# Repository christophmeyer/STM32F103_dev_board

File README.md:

# STM32F103 Development Board

This repo contains the [KiCad](https://www.kicad.org/) hardware design files for a development board for the `STM32F103` MCU, which is somewhat similar to the well known blue pill board. The design(er) has greatly benefitted from some of [Phil Salmony's](https://www.phils-lab.net/) designs :pray:.

## Features

- STM32F103 MCU
  - 2x I2C (pull up resistors included)
  - SPI (22R series termination resistor included)
  - USB micro
  - UART
  - 21 GPIOs
- 16MHz crystal
- ESD protection
- SWD via legged 6-pin plug-of-nails tag-connect connector
- BOOT0 pin toggle switch
- NRST pin push button
- Power LED
- LDO voltage regulator

## Manufacturing

All files necessary for manufacturing the board at the pcb manufacturer of your choice can be found in `./manufacturing_r0.1`. This includes the drill files, gerbers, bill of materials and a basic assembly drawing.

Fully manufactured version of the board:

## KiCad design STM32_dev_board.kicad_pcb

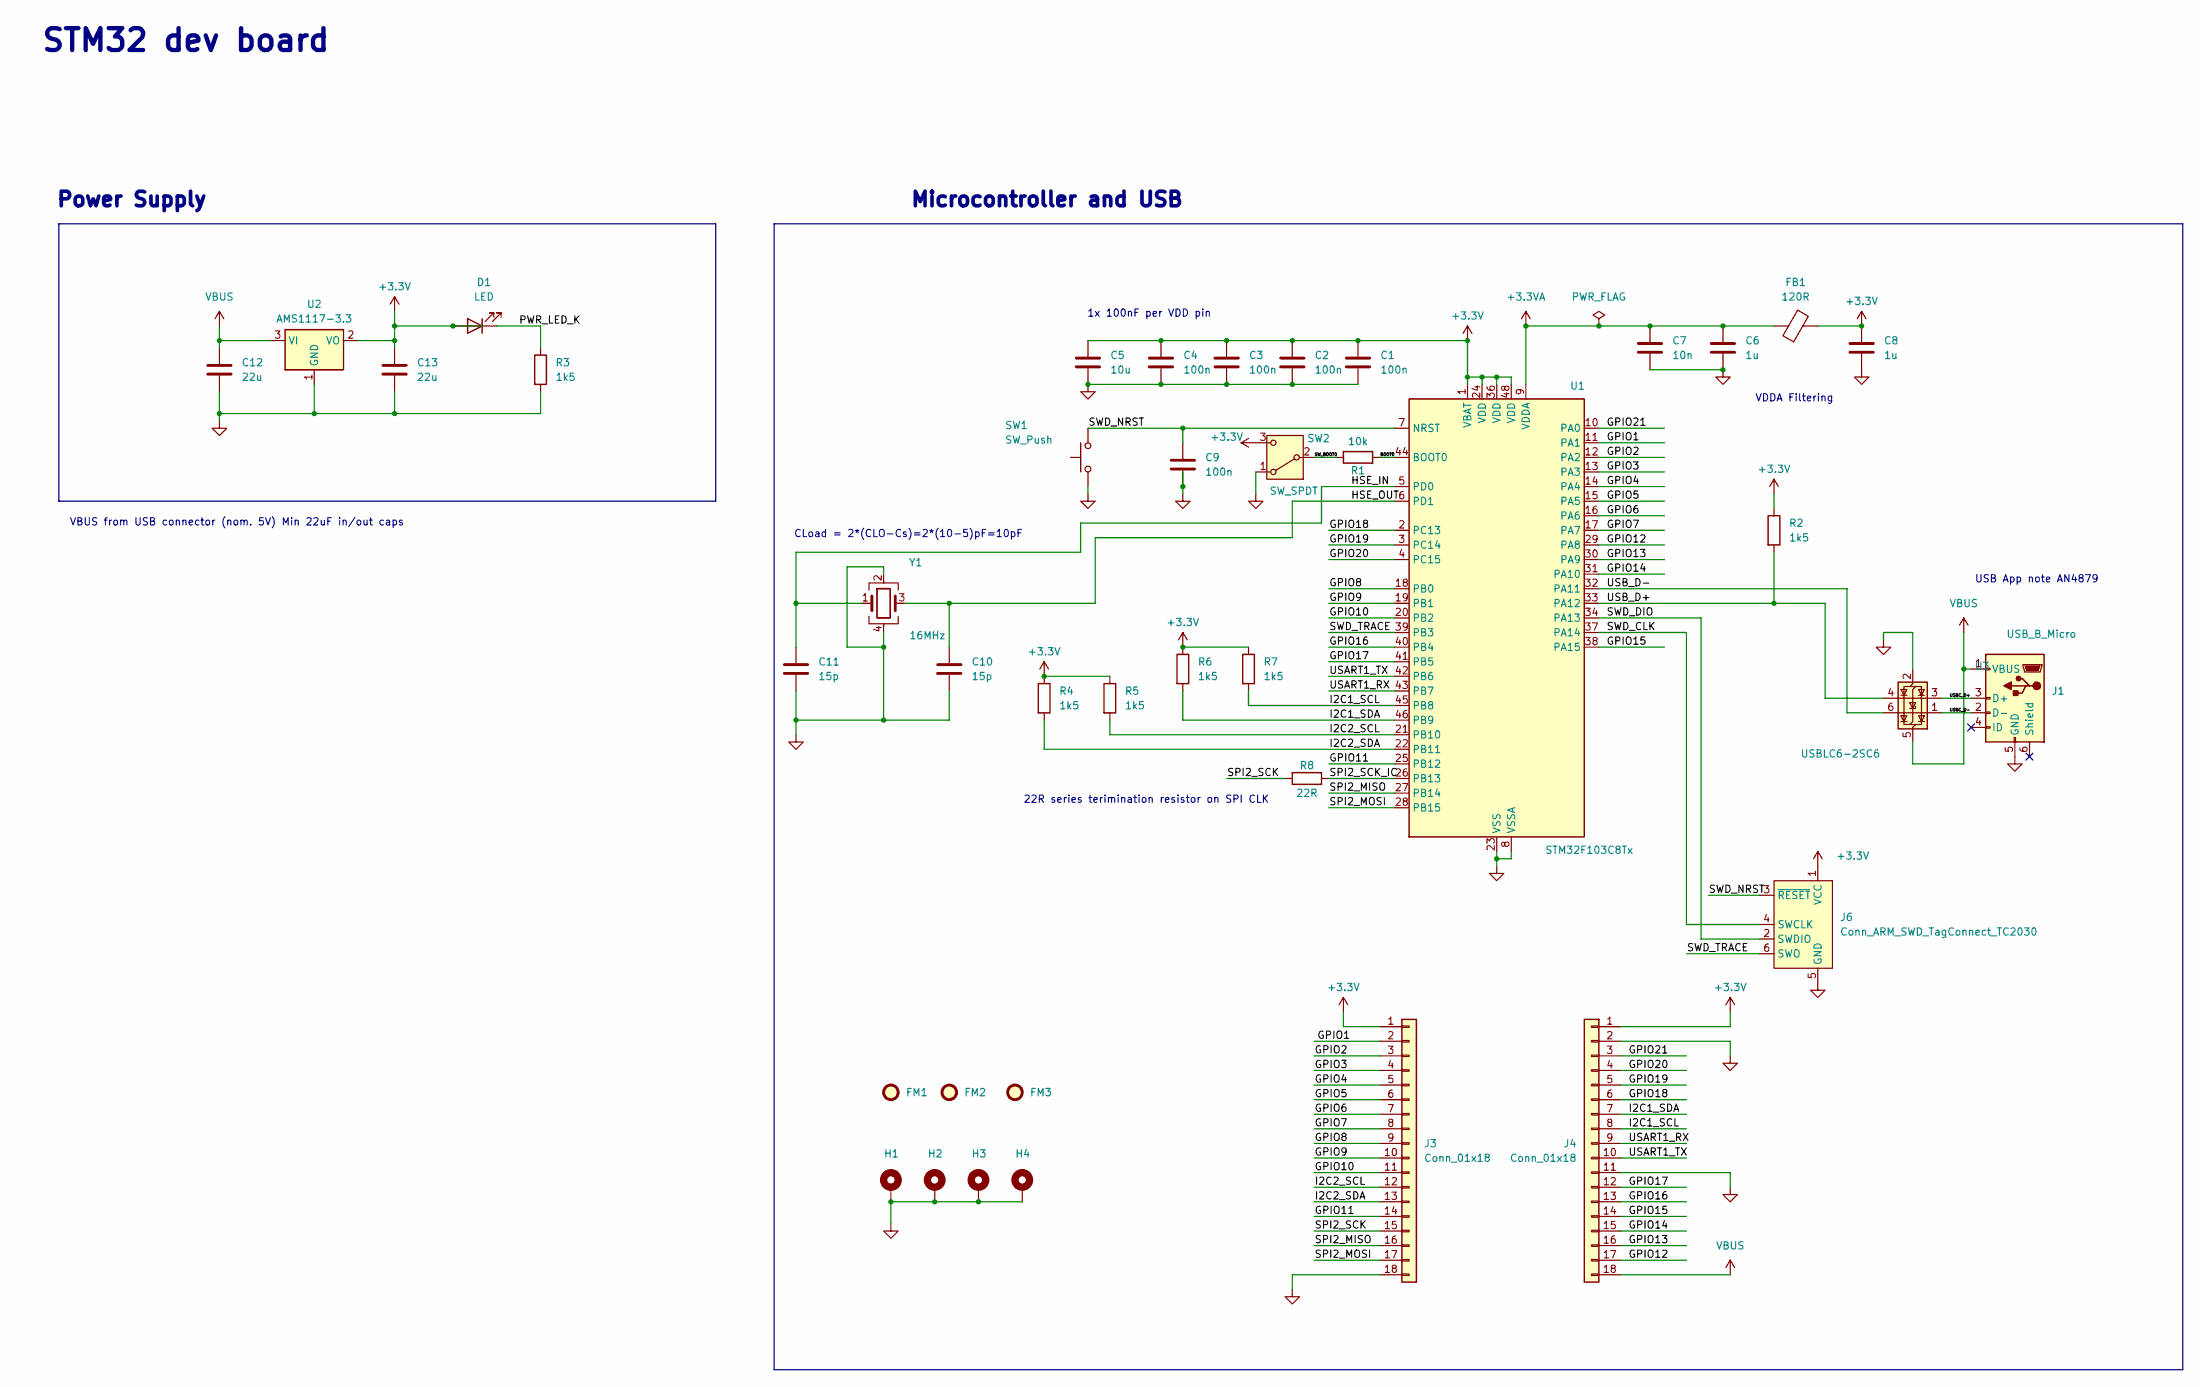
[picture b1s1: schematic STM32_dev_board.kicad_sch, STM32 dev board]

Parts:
C1, C2, C3, C4, C9: 100n; C_0402_1005Metric; Manufacturer Part Number 04023C104KAT2A
C5: 10u; C_0603_1608Metric; Manufacturer Part Number 0603YD106KAT2A
C6, C8: 1u; C_0402_1005Metric; Manufacturer Part Number 04023D105KAT2A
C7: 10n; C_0402_1005Metric; Manufacturer Part Number 0603YD475MAT2A
C10, C11: 15p; C_0402_1005Metric; Manufacturer Part Number 04025U150JAT2A
C12, C13: 22u; C_0805_2012Metric; Manufacturer Part Number 08053D226MAT2A
D1: LED; LED_0603_1608Metric; Manufacturer Part Number 150060SS75000
FB1: 120R; L_0603_1608Metric; Manufacturer Part Number 742792606
FM1, FM2, FM3: Fiducial; Fiducial_1mm_Mask2mm
H1, H2, H3, H4: MountingHole_Pad; MountingHole_2.2mm_M2_Pad_Via
J1: USB_B_Micro; USB_Micro-B_Wuerth_629105150521; Manufacturer Part Number 629105150521
J3, J4: Conn_01x18; PinHeader_1x18_P2.54mm_Vertical
J6: Conn_ARM_SWD_TagConnect_TC2030; Tag-Connect_TC2030-IDC-FP_2x03_P1.27mm_Vertical
R1: 10k; R_0402_1005Metric; Manufacturer Part Number 560112110020
R2, R3, R4, R5, R6, R7: 1k5; R_0402_1005Metric; Manufacturer Part Number 560112110095
R8: 22R; R_0402_1005Metric; Manufacturer Part Number 560112110046
SW1: SW_Push; SW_Push_1P1T_NO_Vertical_Wuerth_434133025816; Manufacturer Part Number 434133025816
SW2: SW_SPDT; SW_SPDT_PCM12; Manufacturer Part Number PCM12SMTR
U1: STM32F103C8Tx; LQFP-48_7x7mm_P0.5mm; Manufacturer Part Number STM32F103C8T6TR
U2: AMS1117-3.3; SOT-223-3_TabPin2; Manufacturer Part Number AMS1117-3.3
U3: USBLC6-2SC6; SOT-23-6; Manufacturer Part Number USBLC6-2SC6Y
Y1: 16MHz; Crystal_SMD_3225-4Pin_3.2x2.5mm; Manufacturer Part Number NX3225GA-16.000M-STD-CRG-2

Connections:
+3.3V: C1.1, C2.1, C3.1, C4.1, C5.1, C8.1, C13.1, D1.2 (A), FB1.2, J3.1, J4.1, J6.1 (VCC), R2.1, R4.1, R5.1, R6.1, R7.1, SW2.3 (C), U1.1 (VBAT), U1.24 (VDD), U1.36 (VDD), U1.48 (VDD), U2.2 (VO)
+3.3VA: C6.1, C7.1, FB1.1, U1.9 (VDDA)
/BOOT0: R1.2, U1.44 (BOOT0)
/GPIO1: J3.2, U1.11 (PA1)
/GPIO2: J3.3, U1.12 (PA2)
/GPIO3: J3.4, U1.13 (PA3)
/GPIO4: J3.5, U1.14 (PA4)
/GPIO5: J3.6, U1.15 (PA5)
/GPIO6: J3.7, U1.16 (PA6)
/GPIO7: J3.8, U1.17 (PA7)
/GPIO8: J3.9, U1.18 (PB0)
/GPIO9: J3.10, U1.19 (PB1)
/GPIO10: J3.11, U1.20 (PB2)
/GPIO11: J3.14, U1.25 (PB12)
/GPIO12: J4.17, U1.29 (PA8)
/GPIO13: J4.16, U1.30 (PA9)
/GPIO14: J4.15, U1.31 (PA10)
/GPIO15: J4.14, U1.38 (PA15)
/GPIO16: J4.13, U1.40 (PB4)
/GPIO17: J4.12, U1.41 (PB5)
/GPIO18: J4.6, U1.2 (PC13)
/GPIO19: J4.5, U1.3 (PC14)
/GPIO20: J4.4, U1.4 (PC15)
/GPIO21: J4.3, U1.10 (PA0)
/HSE_IN: C11.1, U1.5 (PD0), Y1.1
/HSE_OUT: C10.1, U1.6 (PD1), Y1.3
/I2C1_SCL: J4.8, R7.2, U1.45 (PB8)
/I2C1_SDA: J4.7, R6.2, U1.46 (PB9)
/I2C2_SCL: J3.12, R5.2, U1.21 (PB10)
/I2C2_SDA: J3.13, R4.2, U1.22 (PB11)
/PWR_LED_K: D1.1 (K), R3.1
/SPI2_MISO: J3.16, U1.27 (PB14)
/SPI2_MOSI: J3.17, U1.28 (PB15)
/SPI2_SCK: J3.15, R8.2
/SPI2_SCK_IC: R8.1, U1.26 (PB13)
/SWD_CLK: J6.4 (SWCLK), U1.37 (PA14)
/SWD_DIO: J6.2 (SWDIO), U1.34 (PA13)
/SWD_NRST: C9.1, J6.3 (~RESET), SW1.2, U1.7 (NRST)
/SWD_TRACE: J6.6 (SWO), U1.39 (PB3)
/SW_BOOT0: R1.1, SW2.2 (B)
/USART1_RX: J4.9, U1.43 (PB7)
/USART1_TX: J4.10, U1.42 (PB6)
/USBC_D+: J1.3 (D+), U3.3 (I/O2)
/USBC_D-: J1.2 (D-), U3.1 (I/O1)
/USB_D+: R2.2, U1.33 (PA12), U3.4 (I/O2)
/USB_D-: U1.32 (PA11), U3.6 (I/O1)
GND: C1.2, C2.2, C3.2, C4.2, C5.2, C6.2, C7.2, C8.2, C9.2, C10.2, C11.2, C12.2, C13.2, H1.1, H2.1, H3.1, H4.1, J1.5 (GND), J3.18, J4.2, J4.11, J6.5 (GND), R3.2, SW1.1, SW2.1 (A), U1.8 (VSSA), U1.23 (VSS), U1.35 (VSS), U1.47 (VSS), U2.1 (GND), U3.2 (GND), Y1.2, Y1.4
VBUS: C12.1, J1.1 (VBUS), J4.18, U2.3 (VI), U3.5 (VBUS)

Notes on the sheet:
Power Supply
VDDA Filtering
1x 100nF per VDD pin
VBUS from USB connector (nom. 5V) Min 22uF in/out caps
STM32 dev board
USB App note AN4879
22R series terimination resistor on SPI CLK
Microcontroller and USB
CLoad = 2*(CLO-Cs)=2*(10-5)pF=10pF

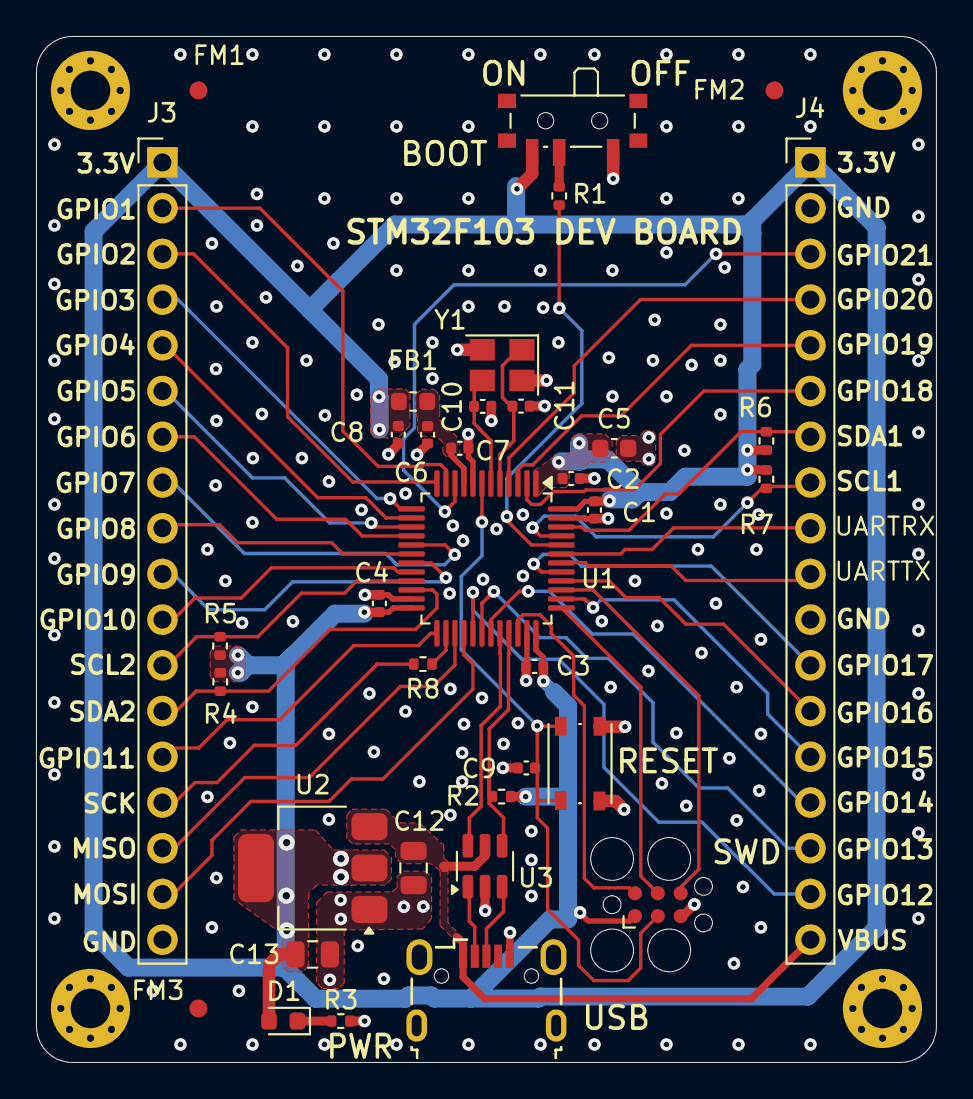
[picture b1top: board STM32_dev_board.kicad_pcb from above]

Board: 4 copper layers, 50.0 x 57.0 mm, 40 parts (0 on the bottom side), 48 nets.

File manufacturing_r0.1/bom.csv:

Reference,Value,Datasheet,Footprint,Qty,Description,Manufacturer,Manufacturer Part Number,Distributor Link,Distributor Part Number
"C1,C2,C3,C4,C9",100n,~,Capacitor_SMD:C_0402_1005Metric,5,Unpolarized capacitor,KYOCERA AVX,04023C104KAT2A,https://www.mouser.de/ProductDetail/KYOCERA-AVX/04023C104KAT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,581-04023C104KAT2A
C5,10u,~,Capacitor_SMD:C_0603_1608Metric,1,Unpolarized capacitor,KYOCERA AVX,0603YD106KAT2A,https://www.mouser.de/ProductDetail/KYOCERA-AVX/0603YD106KAT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,581-0603YD106KAT2A 
"C6,C8",1u,~,Capacitor_SMD:C_0402_1005Metric,2,Unpolarized capacitor,KYOCERA AVX,04023D105KAT2A,https://www.mouser.de/ProductDetail/KYOCERA-AVX/04023D105KAT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,581-04023D105KAT2A
C7,10n,~,Capacitor_SMD:C_0402_1005Metric,1,Unpolarized capacitor,KYOCERA AVX,0402YC104JAT4A,https://eu.mouser.com/ProductDetail/KYOCERA-AVX/0402YC104JAT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,581-0402YC104JAT4A
"C10,C11",15p,~,Capacitor_SMD:C_0402_1005Metric,2,Unpolarized capacitor,KYOCERA AVX,04025U150JAT2A,https://www.mouser.de/ProductDetail/KYOCERA-AVX/04025U150JAT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,
"C12,C13",22u,~,Capacitor_SMD:C_0805_2012Metric,2,Unpolarized capacitor,KYOCERA AVX,08053D226MAT2A,https://www.mouser.de/ProductDetail/KYOCERA-AVX/08053D226MAT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,581-08053D226MAT2A 
D1,LED,~,LED_SMD:LED_0603_1608Metric,1,Light emitting diode,Würth Elektronik,150060SS75000,https://www.digikey.de/en/products/detail/w%C3%BCrth-elektro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,732-4979-2-ND
FB1,120R,~,Inductor_SMD:L_0603_1608Metric,1,Ferrite bead,Würth Elektronik,742792606,https://www.mouser.de/ProductDetail/Wurth-Elektronik/7427926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,710-742792606
J1,USB_B_Micro,~,Connector_USB:USB_Micro-B_Wuerth_629105150521,1,USB Micro Type B connector,Würth Elektronik,629105150521,https://www.digikey.de/en/products/detail/w%C3%BCrth-elektro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,732-5960-2-ND
R1,10k,~,Resistor_SMD:R_0402_1005Metric,1,Resistor,Würth Elektronik,560112110020,https://www.mouser.de/ProductDetail/Wurth-Elektronik/5601121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,710-560112110020 
"R2,R3,R4,R5,R6,R7",1k5,~,Resistor_SMD:R_0402_1005Metric,6,Resistor,Würth Elektronik,560112110095,https://www.mouser.de/ProductDetail/Wurth-Elektronik/5601121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,710-560112110095 
R8,22R,~,Resistor_SMD:R_0402_1005Metric,1,Resistor,Würth Elektronik,560112110046,https://www.mouser.de/ProductDetail/Wurth-Elektronik/5601121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,710-560112110046 
SW1,SW_Push,~,Button_Switch_SMD:SW_Push_1P1T_NO_Vertical_Wuerth_434133025816,1,"Push button switch, generic, two pins",Würth Elektronik,434133025816,https://www.digikey.de/en/products/detail/w%C3%BCrth-elektro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,732-13663-2-ND
SW2,SW_SPDT,~,Button_Switch_SMD:SW_SPDT_PCM12,1,"Switch, single pole double throw",C&K,PCM12SMTR,https://www.digikey.com/en/products/detail/c-k/PCM12SMTR/1640112,401-2016-2-ND
U1,STM32F103C8Tx,https://www.st.com/resource/en/datasheet/stm32f103c8.pdf,Package_QFP:LQFP-48_7x7mm_P0.5mm,1,"STMicroelectronics Arm Cortex-M3 MCU, 64KB flash, 20KB RAM, 72 MHz, 2.0-3.6V, 37 GPIO, LQFP48",STMicroelectronics,STM32F103C8T6TR,https://www.digikey.com/en/products/detail/stmicroelectronic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,497-17666-2-ND
U2,AMS1117-3.3,http://www.advanced-monolithic.com/pdf/ds1117.pdf,Package_TO_SOT_SMD:SOT-223-3_TabPin2,1,"1A Low Dropout regulator, positive, 3.3V fixed output, SOT-223", UMW,AMS1117-3.3,https://www.digikey.de/en/products/detail/umw/AMS1117-3-3/17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,4518-AMS1117-3.3TR-ND
U3,USBLC6-2SC6,https://www.st.com/resource/en/datasheet/usblc6-2.pdf,Package_TO_SOT_SMD:SOT-23-6,1,"Very low capacitance ESD protection diode, 2 data-line, SOT-23-6",STMicroelectronics,USBLC6-2SC6Y,https://www.mouser.de/ProductDetail/STMicroelectronics/USBLC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,511-USBLC6-2SC6Y
Y1,16MHz,~,Crystal:Crystal_SMD_3225-4Pin_3.2x2.5mm,1,"Four pin crystal, GND on pins 2 and 4",NDK,NX3225GA-16.000M-STD-CRG-2,https://www.mouser.in/ProductDetail/NDK/NX3225GA-16.000M-STD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,344-NX3225GA16MCRG2
